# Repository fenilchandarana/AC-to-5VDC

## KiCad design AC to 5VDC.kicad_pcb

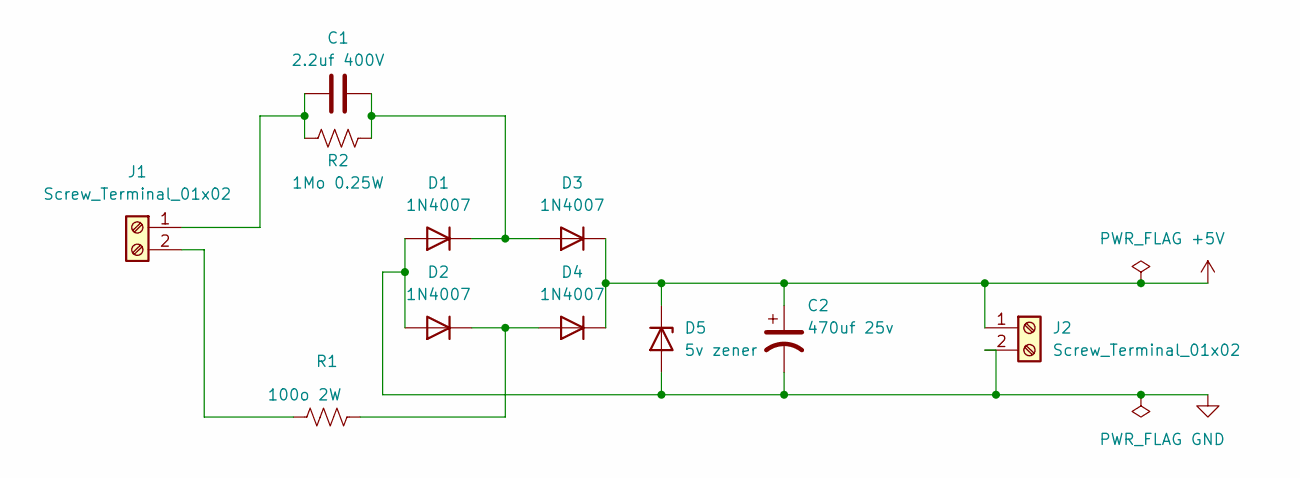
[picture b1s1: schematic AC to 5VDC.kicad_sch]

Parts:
C1: 2.2uf 400V; C_Rect_L24.0mm_W8.6mm_P22.50mm_MKT
C2: 470uf 25v; CP_Radial_D10.0mm_P5.00mm
D1, D2, D3, D4: 1N4007; D_A-405_P7.62mm_Horizontal
D5: 5v zener; D_A-405_P7.62mm_Horizontal
J1, J2: Screw_Terminal_01x02; TerminalBlock_bornier-2_P5.08mm
R1: 100o 2W; R_Axial_DIN0614_L14.3mm_D5.7mm_P20.32mm_Horizontal
R2: 1Mo 0.25W; R_Axial_DIN0207_L6.3mm_D2.5mm_P10.16mm_Horizontal

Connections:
+5V: C2.1, D3.1 (K), D4.1 (K), D5.1 (K), J2.1
GND: C2.2, D1.2 (A), D2.2 (A), D5.2 (A), J2.2
unnamed: C1.1, J1.1, R2.1
unnamed: C1.2, D1.1 (K), D3.2 (A), R2.2
unnamed: D2.1 (K), D4.2 (A), R1.2
unnamed: J1.2, R1.1

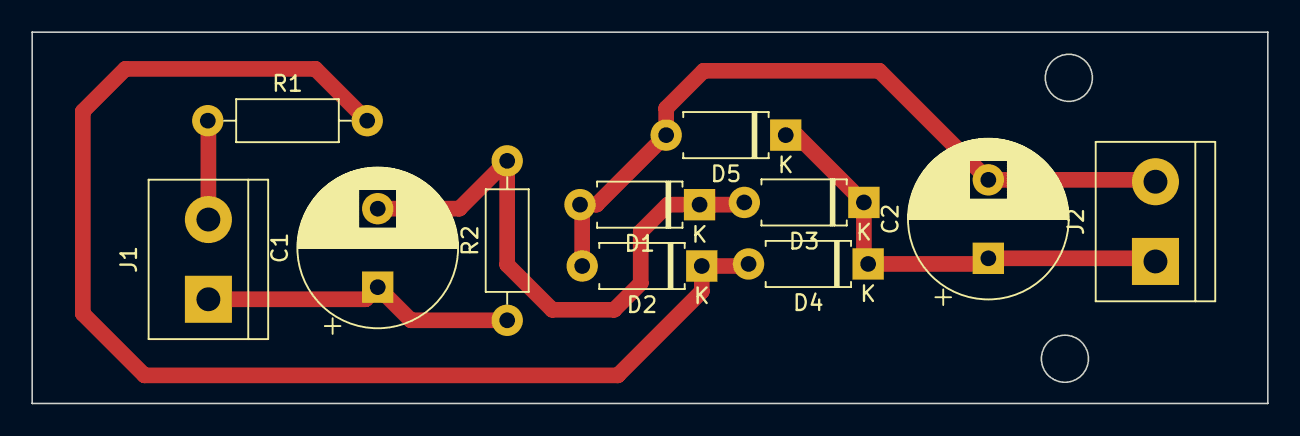
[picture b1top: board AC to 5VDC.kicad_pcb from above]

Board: 2 copper layers, 78.7 x 23.7 mm, 11 parts (0 on the bottom side), 6 nets.

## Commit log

2024-01-10 changed the assigned footprints
2024-08-25 some changes in project file. Post cdrive fuckup
